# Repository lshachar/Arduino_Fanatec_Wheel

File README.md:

# Arduino_Fanatec_Wheel
A do-it-yourself steering wheel to Fanatec's wheel base.<br/><br/>
**29.10.2020** Run the project on a 3.3V Arduino without a logic shifter<br/>

[more info here](Pro%20Mini%20V2%203.3V/README.md)

*You can run the code on a 3.3V Arduino without the need for a logic shifter. This allows for a small enough pcb and 3D model to hold it, which you can then mount onto your custom wheel. Because the model is only 16mm high you won't have any space issues.
________________
**28.04.2020 Coronavirus update:** Version 1 is out!<br/>

[check out more photos here](https://github.com/lshachar/Arduino_Fanatec_Wheel/tree/master/Steering%20Wheel%20Photos)

*The buttons delay bug is fixed, buttons code is working great!<br/>
*I fixed several large bugs with the SPI communication, which now works flawlessly.<br/>
*Updated schematics - Added a 5 buttons Analog input that feeds into a single analog input on the arduino. You can calibrate your wheel center by using the D-pad and alphanumeric display, without plugging the Arduino to your PC!<br/>
*Added Diode, and connected D2 and D10 together, both changes are necessary! please revise your board to include these changes if you've built one already!<br/>
*Updated board layout - it's possible to either manufacture a single layer board, and solder a few jumper wires for the top layer, or manufacture the complete two-layers board. (I used a CNC machine and milled a single layer board)
________________

**This project is donationware, if my work helped you out** [**maybe get me a beer! :)**](https://paypal.me/lshachar)<br/><br/>
  
Fanatec's wheelbases won't enable any force feedback, unless you have a Fanatec steering wheel attached to it.
With this project, you can use an arduino to communicate with the wheelbase over SPI, which will get the wheelbase working.
You can attach buttons, a D-Pad and an alphanumeric display, for the complete package!

This simplified (schematics) version is enough to let you enable force feedback on your wheelbase,
[use this easy to understand 'breadboard view' simplified schematics](https://github.com/lshachar/Arduino_Fanatec_Wheel/blob/master/schamtics%20arduino%20nano-level%20shifter-fanatec%20round%20plug.png), or [This simplified schematic](https://github.com/lshachar/Arduino_Fanatec_Wheel/blob/master/schamtics%20arduino%20nano-level%20shifter-Simlified.png).

The full PCB supports alphanumeric display, D-pad, and lots of external buttons
 (I currently use 6: 2 paddle shifters and 4 buttons on the rim).

Here's a [how to make a male Fanatec SPI connector](Steering%20wheel%20connector%20-%20howto/Readme.md) (what the steering wheel has)<br/>
Also, [Alevale found where to buy the connector](https://github.com/darknao/btClubSportWheel/issues/14#issuecomment-604973137)<br/><br/>
[use this](3d%20Models/fanatec%20adapter%20v1.STL) If you need a simple 3d adapter to attach your physical steering wheel to the wheelbase<br/><br/>

### Several options:
- Use a 5V arduino with a logic level shifter. (recommended, this is what I use. [(here are The schematics)](https://github.com/lshachar/Arduino_Fanatec_Wheel/blob/master/schamtics%20arduino%20nano-level%20shifter-fanatec%20round%20plug.png)
- Use a 5V arduino **without** a logic shifter (can be risky to your precious wheelbase)
- Use a 3.3V arduino (You will need an Arduino Pro Mini V2 which runs 3.3V at 16 MHz, as 8 MHz is not fast enough. For a more detailed guide [please read this](Pro%20Mini%20V2%203.3V/README.md))

Code was tested on arduino Uno and Nano, and works fine. However, they both output 5V and the SPI communication on the wheelbase
is using 3.3V.
It's best to use a level shifter between the two, so there are no chances of damaging the wheelbase (by connecting the 5V arduino 
output to a 3.3V wheelbase input)
However, since the wheelbase is the master and the steering wheel is the slave - MISO is the only *input* channel on the wheelbase,
and it is safe to simply use a voltage divider on the MISO line - to go from 5V level to 3.3V. (The arduino should recognize the 3.3V input signals coming from the wheelbase as high, so there's nothing we have to do there). <br/>
- **Note:** If you do end up going this route, make sure you wire everything up properly, and that you never set SPI as master on the arduino, or you will subject the wheelbase SPI to 5V. (I did subject the wheelbase SPI to 5V by mistake - and nothing got damaged.)<br/><br/>

I recommend using an arduino nano **and** a logic shifter, as seen in the schematics.
- **Note:** The diode is crucial to keep the 5V coming from the wheelbase, and the 5V coming from the computer USB, seperate. the diode will drop the 5V voltage from the wheelbase to ~4.3V, which is fine for the arduino to run on. When you plug the USB cable, the arduino will run on the 5V coming from the computer, and current cannot flow to the wheelbase because of the diode.<br/>
fyi I have connected both power supplies together, and did not have anything go up in smoke. (but this is before I thought about using a diode. DO NOT ATTEMPT THIS YOURSELF.<br/>

[There's a lot of (old) info here](https://github.com/darknao/btClubSportWheel/issues/12)

# What to do if you gotta calibrate your wheelbase center?
On some wheelbases, you can do that directly from the [Fanatec wheel properties page](https://github.com/lshachar/Arduino_Fanatec_Wheel/issues/7). unfortunately it doesn't work on my CSW V2.5.<br/>
You can use the current code to calibrate the wheelbase's center point. (This is needed after a firmware upgrade for the wheelbase) the arduino will translate the alphanumeric display to letters and send them out to the Serial monitor(!). you will need to type in some commands on the Serial monitor, which will look pretty cypheric to you.
Type these characters on the serial monitor, press [return] after each line: <br/><br/>
C		(to change bits on the 3rd byte that affects buttons. C=3rd)
6		(to change (raise) the sixth bit on the 3rd byte, which is the menu button. this will cause the alphanumeric display to turn on and the message '5_1' (equivilent to 'S_1' i.e. 'setting 1') will be printed on the serial monitor.)  
6		(to release the menu button (lower the 6th bit) )  
23		(2 will raise the D-pad button bit, 3 will raise the joystick button bit.)  
23		(to release both buttons, drop both bits)
6		(press the menu button again to exit the menu)  
6		(release the menu button)  
[Watch this If you don't know what I'm talking about](https://www.youtube.com/watch?v=yvhAKxjit8o)  
(Hey - it's not an easy procedure, but it works!)
if you made a PCB with a Dpad and alphanumeric display - you can calibrate the center point without connecting to the computer!
Using the Dpad:
Enter the menu by pressing both up+down bubttons on the Dpad,
S_1 will appear on the serial monitor and on the alphanumeric display,
Press both left+right buttons on the Dpad to calibrate wheel center,
Press both up+down on the Dpad to exit menu. Done!

This project would never have been possible without the work of Darknao on his [BtClubSportWheel - converting any Fanatec CSW steering wheel to a standalone USB version](https://github.com/darknao/btClubSportWheel) project.

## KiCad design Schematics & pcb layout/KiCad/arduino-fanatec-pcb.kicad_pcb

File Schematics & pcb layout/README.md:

I'm keeping the legacy PCB layouts here, as someone may want to use the version 'without display or Dpad' for simplicity.<br/>
please look inside KiCad for the most recent version.<br/>
check out Steering Wheel Photos folder, for photos describing how I have everything connected.<br/><br/>

I did not manufacture this PCB properly in a factory, but rather I milled it on a CNC machine. I used a single layer PCB (for the buttom layer in green), and the top side (red)
was meant to be connected with some jumper wires.<br/>
So, I was using vias on the design as plated through-holes, as means to attach wires to. (AFAIK there will not be holes if you sent the gerber files to a factory. The PCB layout file must be edited to create a hole first!)<br/>
note that I didn't even bother placing some of the lines (appear as white lines in the layout file) since jumper wires can easily cross over each other. with a bit of editing, all these things can be fixed so that you could get a good working PCB right from the factory.<br/>
I see that not all TM1637 display boards have the same connector, you might need to switch the order of some of the pins, or move them from the top right corner of the PCB, towards the D pad buttons, on the top left of the PCB.<br/>
The diode solves the issue I had with connectiong the wheelbase's 5V supply with the USB 5v supply coming from the computer, so it's really important.<br/>
you can use almost all the pins on the large breakout connector (J3) for buttons, except the last two - D0 and D1 on arduino are also the serial communication pins. so they are there just for debugging.<br/>
It would be useful to add another row of 8 pins to the left of J1, in order to have breakout pins for the SPI communications with the wheelbase. <br/>
AREF - there is a via, but it's not used. (it was connected to the + side of the diode, (there is a via there as well)) but it's not used. In fact, using it would create problems with the dpad buttons that are on the layout.<br/><br/>

Good luck!

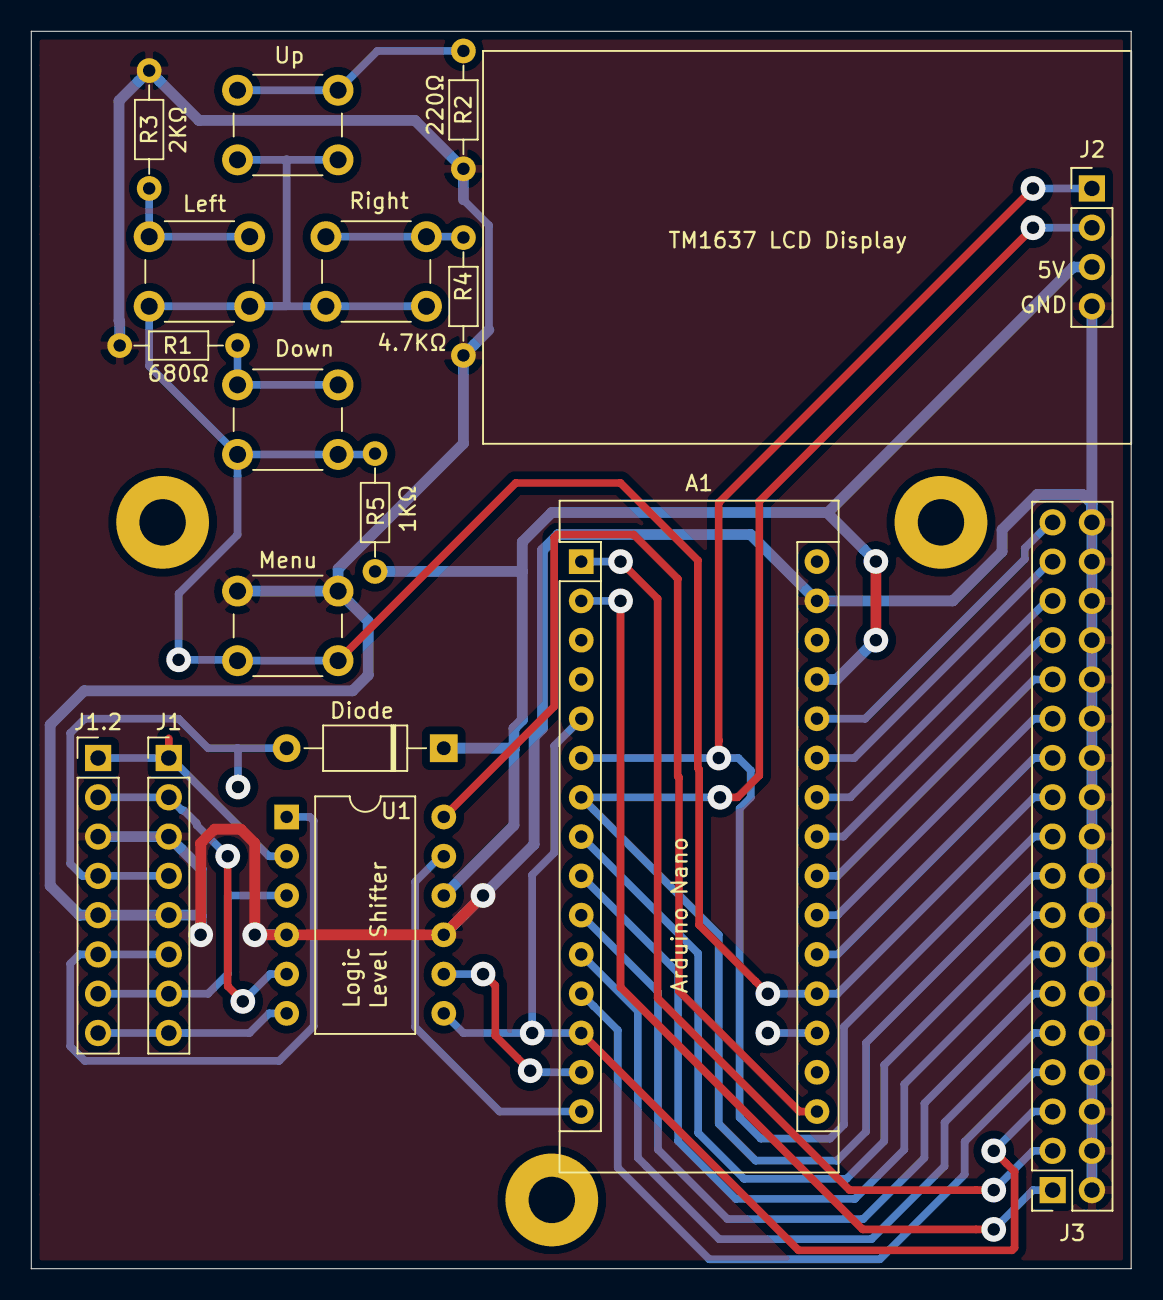
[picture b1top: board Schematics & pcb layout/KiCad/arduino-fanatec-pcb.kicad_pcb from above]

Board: 2 copper layers, 71.1 x 80.0 mm, 20 parts (0 on the bottom side), 33 nets.

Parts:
A1: Arduino_Nano_v3.x; Arduino_Nano
Diode: .; D_A-405_P10.16mm_Horizontal
Down: SW_Push; SW_PUSH_6mm
H1, H1#2, H1#3: MountingHole; MountingHole_3mm_Pad
J1: SPI Connector 01x08_Male; PinHeader_1x08_P2.54mm_Vertical
J1.2: Extra pin breakout; PinHeader_1x08_P2.54mm_Vertical
J2: TM1637 4 digit Display connector; PinHeader_1x04_P2.54mm_Vertical
J3: Breakout Connector 02x18_Odd_Even; PinSocket_2x18_P2.54mm_Vertical
Left: SW_Push; SW_PUSH_6mm
Level Shifter: Simple_Chinese_Logic_level_shifter; DIP-12_W10.16mm
Menu: SW_Push; SW_PUSH_6mm
R1: 680; R_Axial_DIN0204_L3.6mm_D1.6mm_P7.62mm_Horizontal
R2: 220; R_Axial_DIN0204_L3.6mm_D1.6mm_P7.62mm_Horizontal
R3: 2k; R_Axial_DIN0204_L3.6mm_D1.6mm_P7.62mm_Horizontal
R4: 4.7k; R_Axial_DIN0204_L3.6mm_D1.6mm_P7.62mm_Horizontal
R5: 1K; R_Axial_DIN0204_L3.6mm_D1.6mm_P7.62mm_Horizontal
Right: SW_Push; SW_PUSH_6mm
Up: SW_Push; SW_PUSH_6mm

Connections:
/5V: A1.27, Diode.1, J2.3, Level Shifter.11, R5.2
/D0: A1.2, J3.1
/D1: A1.1, J3.3
/D5: A1.8, J3.15
/D6: A1.9, J3.13
/D7: A1.10, J3.11
/D8: A1.11, J3.9
/D9: A1.12, J3.7
/D10: A1.5, A1.13, J3.5, Level Shifter.7
/Dpad: A1.19, Down.2, J3.21, Left.2, Menu.2, R5.1, Right.2, Up.2
/TM_CLK: A1.6, J2.1, J3.19
/TM_D: A1.7, J2.2, J3.17
GND: A1.29, J1.3, J1.5, J1.2.3, J1.2.5, J2.4, J3.2, J3.4, J3.6, J3.8, J3.10, J3.12, J3.14, J3.16, J3.18, J3.20, J3.22, J3.24, J3.26, J3.28, J3.30, J3.32, J3.34, J3.36, Level Shifter.6, Level Shifter.12, Menu.1, R1.1, R2.1, R3.1, R4.1
unnamed: A1.14, Level Shifter.8
unnamed: A1.15, Level Shifter.9
unnamed: A1.16, Level Shifter.10
unnamed: A1.20, J3.23
unnamed: A1.21, J3.25
unnamed: A1.22, J3.27
unnamed: A1.23, J3.29
unnamed: A1.24, J3.31
unnamed: A1.25, J3.33
unnamed: A1.26, J3.35
unnamed: Diode.2, J1.4, J1.2.4
unnamed: Down.1, R1.2
unnamed: Left.1, R3.2
unnamed: R4.2, Right.1
unnamed: R2.2, Up.1
unnamed: J1.1, J1.2.1, Level Shifter.3
unnamed: J1.2, J1.2.2, Level Shifter.4
unnamed: J1.6, J1.2.6, Level Shifter.2
unnamed: J1.7, J1.2.7, Level Shifter.1
unnamed: J1.8, J1.2.8, Level Shifter.5

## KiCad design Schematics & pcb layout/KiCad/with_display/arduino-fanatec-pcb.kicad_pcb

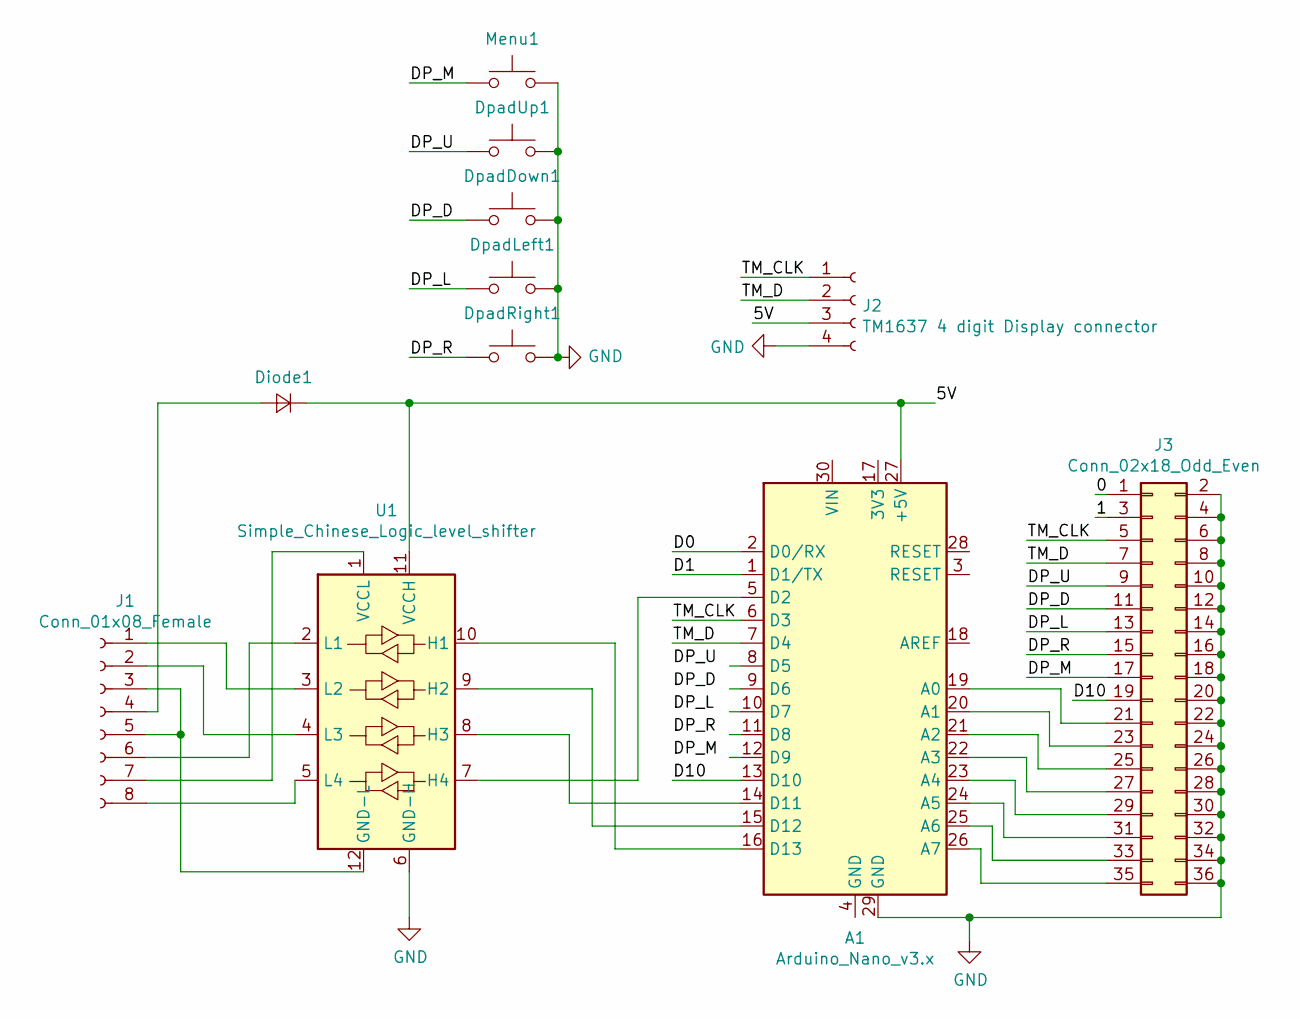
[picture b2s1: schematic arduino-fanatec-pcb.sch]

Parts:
A1: Arduino_Nano_v3.x; Arduino_Nano
Diode1: .; D_5W_P10.16mm_Horizontal
DpadDown1: SW_Push; SW_PUSH_6mm
DpadLeft1: SW_Push; SW_PUSH_6mm
DpadRight1: SW_Push; SW_PUSH_6mm
DpadUp1: SW_Push; SW_PUSH_6mm
J1: Conn_01x08_Female; PinHeader_1x08_P2.54mm_Vertical
J2: TM1637 4 digit Display connector; PinHeader_1x04_P2.54mm_Horizontal
J3: Conn_02x18_Odd_Even; PinSocket_2x18_P2.54mm_Vertical
Menu1: SW_Push; SW_PUSH_6mm
U1: Simple_Chinese_Logic_level_shifter; DIP-12_W10.16mm

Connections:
/0: J3.1
/1: J3.3
/5V: A1.27 (+5V), Diode1.1 (K), J2.3, U1.11 (VCCH)
/D0: A1.2 (D0/RX)
/D1: A1.1 (D1/TX)
/D10: A1.13 (D10), J3.19
/DP_D: DpadDown1.1, J3.11
/DP_L: DpadLeft1.1, J3.13
/DP_M: J3.17, Menu1.1
/DP_R: DpadRight1.1, J3.15
/DP_U: DpadUp1.1, J3.9
/TM_CLK: A1.6 (D3), J2.1, J3.5
/TM_D: A1.7 (D4), J2.2, J3.7
GND: A1.29 (GND), DpadDown1.2, DpadLeft1.2, DpadRight1.2, DpadUp1.2, J2.4, J3.2, J3.4, J3.6, J3.8, J3.10, J3.12, J3.14, J3.16, J3.18, J3.20, J3.22, J3.24, J3.26, J3.28, J3.30, J3.32, J3.34, J3.36, Menu1.2, U1.6 (GND-H)
unnamed: A1.5 (D2), U1.7 (H4)
unnamed: A1.14 (D11), U1.8 (H3)
unnamed: A1.15 (D12), U1.9 (H2)
unnamed: A1.16 (D13), U1.10 (H1)
unnamed: A1.19 (A0), J3.21
unnamed: A1.20 (A1), J3.23
unnamed: A1.21 (A2), J3.25
unnamed: A1.22 (A3), J3.27
unnamed: A1.23 (A4), J3.29
unnamed: A1.24 (A5), J3.31
unnamed: A1.25 (A6), J3.33
unnamed: A1.26 (A7), J3.35
unnamed: Diode1.2 (A), J1.4
unnamed: J1.1, U1.3 (L2)
unnamed: J1.2, U1.4 (L3)
unnamed: J1.3, J1.5, U1.12 (GND-L)
unnamed: J1.6, U1.2 (L1)
unnamed: J1.7, U1.1 (VCCL)
unnamed: J1.8, U1.5 (L4)

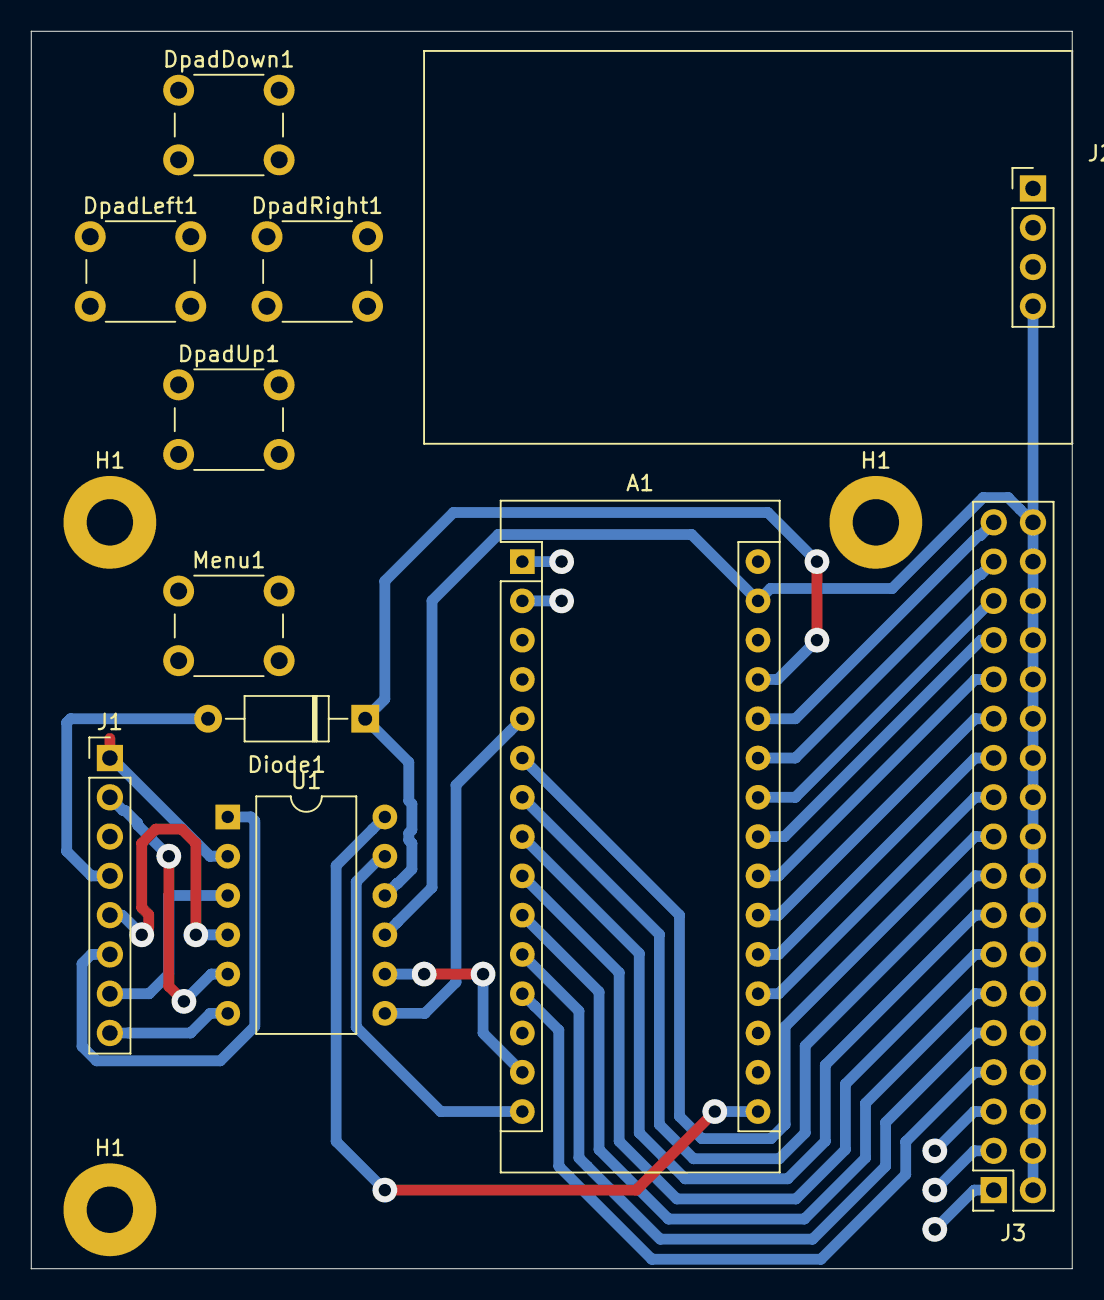
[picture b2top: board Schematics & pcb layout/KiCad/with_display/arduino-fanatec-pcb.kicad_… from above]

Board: 2 copper layers, 67.3 x 80.0 mm, 14 parts (0 on the bottom side), 29 nets.

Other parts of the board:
H1, H1#2, H1#3: MountingHole; MountingHole_3mm_Pad

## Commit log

2019-07-01 Debug code: for some reason when a button is sent, it roughly takes 170ms before it appears in windows. however, the button disappears instantly when that command is sent. connect a buzzer (piezoelec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
2019-07-03 left + right peddals
2019-07-03 FanatecWindowsDisplay init commit
2019-07-03 fix alphanumeric display bug regarding characters that did not change
2019-07-03 This little test helped me make sure that the wheelbase raises the CS line after every time that the buffer is completely read out. (ie if buffer gets read 10 times, CS line will raise 10 times). So 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
2019-07-03 implemented a buffer for the returnData array: when clicking a button there is an ~180 ms delay before the computer receives the command. I thought that buffering the buttons and the crc8 before send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
2019-09-15 readme - arduino nano tested
2019-10-05 Simple schematics to show the connection between Fanatec's round wheelbase plug, a logic shifter, and an Arduino nano. Credit to Jonbakhol
2019-12-31 new schematics and pcb layout. To be manufactured from a single layer board (bottom only). Top can easily be connected with some pieces of wire. (in the 3d screenshot file, the bottom layer is displa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
2019-12-31 Display support: TM1637 chip, 7 segments 4 digits display (only 3 digits are used). buy the display version that has decimal dots next to each digit!
2019-12-31 Added schematics and PCB (work in progress) with 7 segments display and Dpad+menu buttons. Thinking about connecting all these buttons to one analog input, but reading analog inputs takes longer. OTO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
2020-04-10 The PCB now supports the 4 digits alphanumeric display and 5 buttons D-pad, which are read by a single analog pin on the arduino. see README.md in schematics & pcb layout for more information about t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
2020-04-13 debugging the cable select pin
2020-04-13 button debugging, for digital / analog buttons that are each connected to a single input on the arduino (with internal input pullup, and ground connection)
2020-04-13 working nicely
2020-04-27 Cleanup
2020-04-27 print dpad value on alphanumeric display - nicer & simpler
2020-04-27 buttons and Dpad code now uses sensible functions
2020-04-28 updated PCB layout and schematics, including Dpad, Alphanumeric display, buttons, Diode - and many bug fixes
2020-11-01 Closes #9 Update readme, provide images, pcb and 3d qr adapter model
2020-11-15 #9 Update readme and PCB files
    - add wheelbase damage warning
    - add note to uncomment lines
    - remove connection of 5V to RAW (including diode)
2022-03-13 see https://github.com/lshachar/Arduino_Fanatec_Wheel/issues/20
2022-12-19 Updated the PCB front silkscreen, exported Geber files for manufacturing according to jlcpcb's requirements
2023-01-04 new: "CRC8 Match" messages will be generated on the serial connection, for easier debugging of the SPI interface, which is the issue most users experience. I am getting somewhere between 10 to 200 "m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
2023-01-04 bug solved (with debug code)
2023-01-04 Fixing alphanumeric display jittering: when packet was received with a bad crc8, do not display the text on the alphanumeric display. For the serial monitor, you can uncomment the line: #define DISPL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
